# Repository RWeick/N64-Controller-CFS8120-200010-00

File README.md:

# N64-Controller-CFS8120-200010-00
The Kicad files for one variant of the N64 Controller PCB

PCB Thickness: 1.6 mm

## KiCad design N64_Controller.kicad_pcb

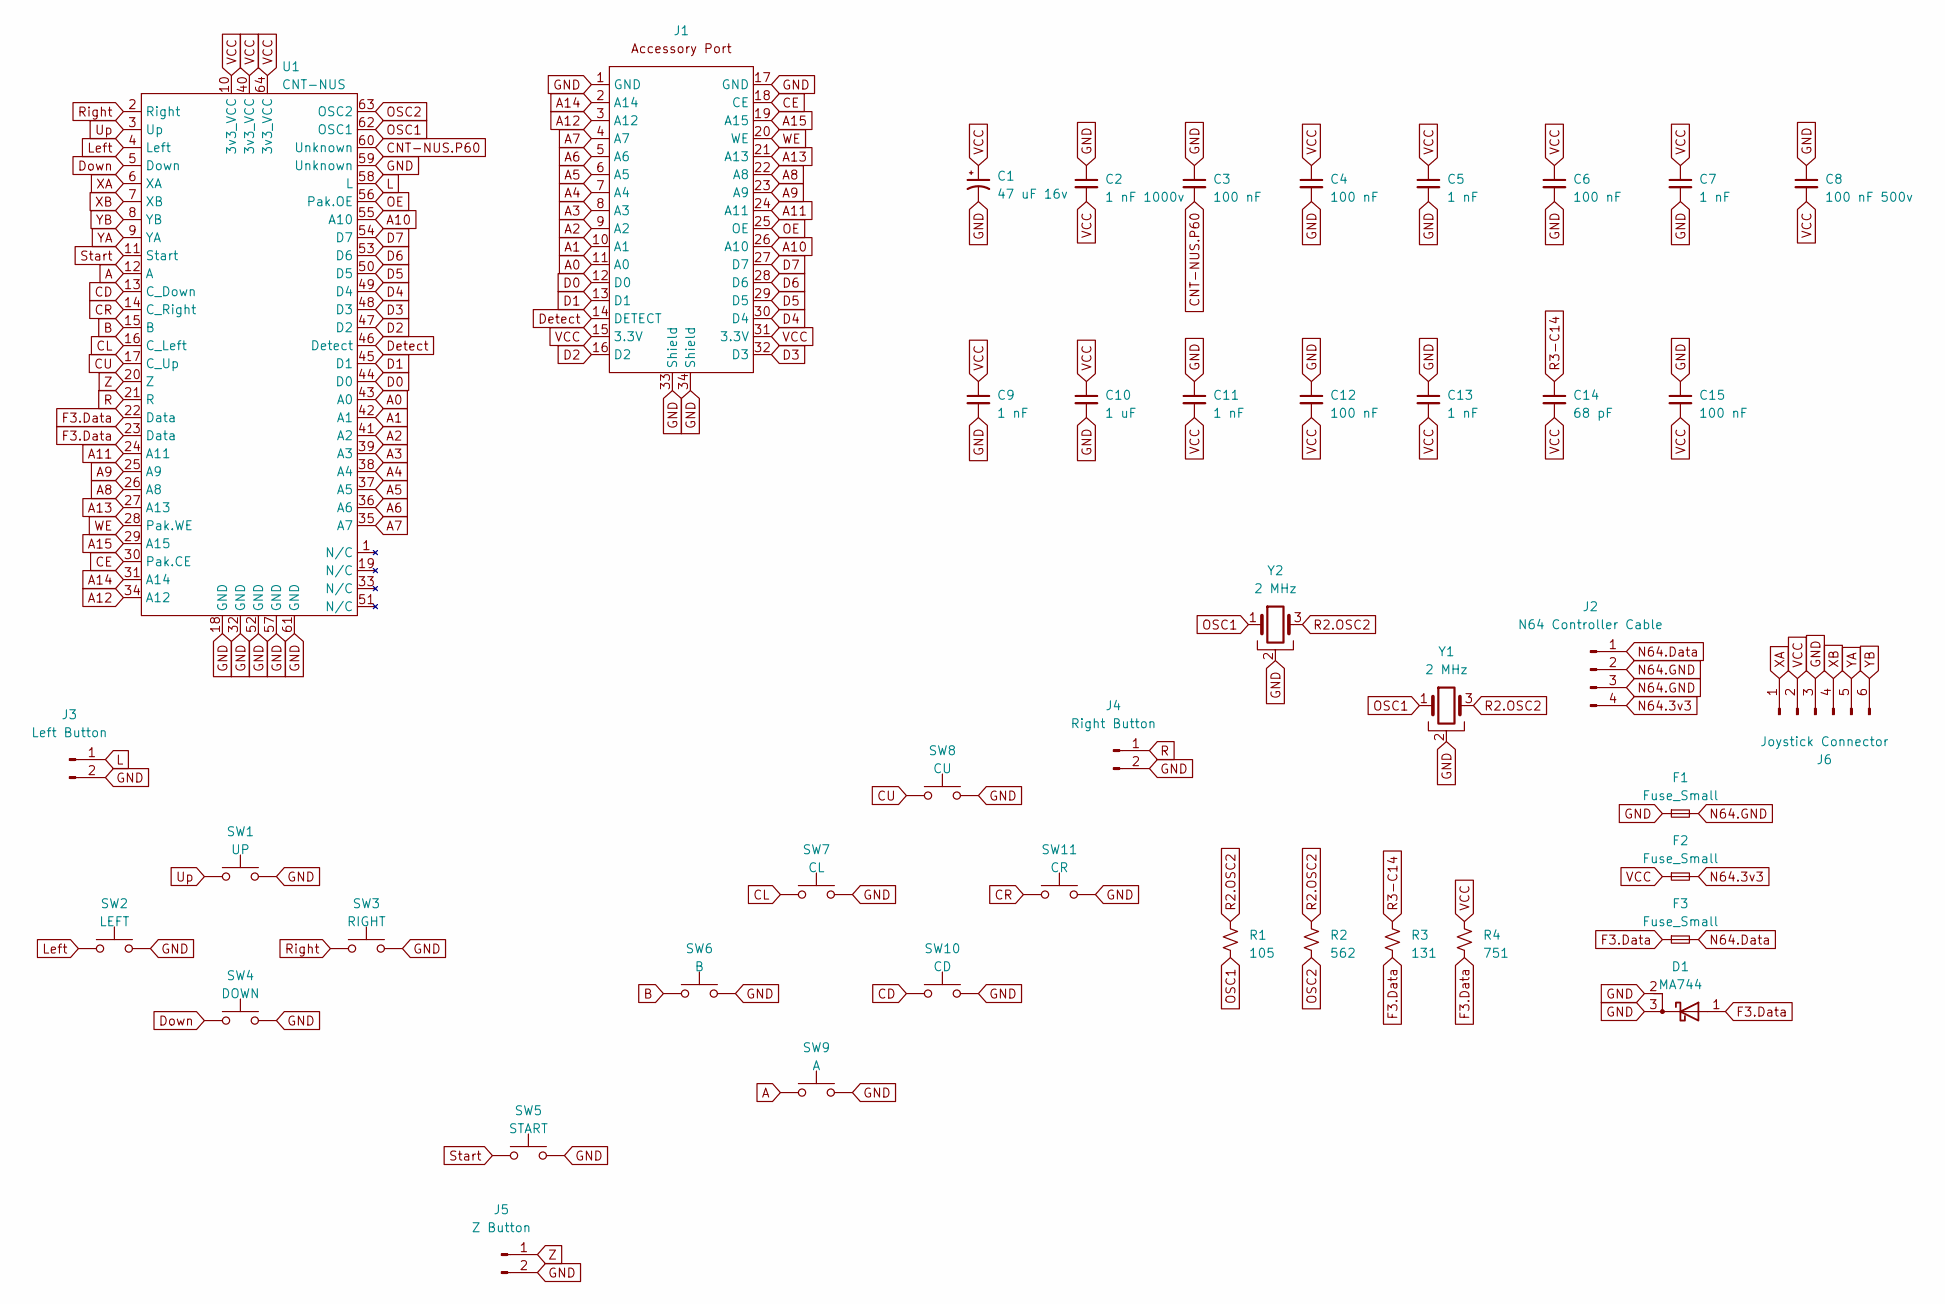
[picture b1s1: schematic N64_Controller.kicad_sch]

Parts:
C1: 47 uF 16v; CP_Radial_D5.0mm_P2.50mm
C2: 1 nF 1000v; TH Capacitor
C3, C4, C6, C12, C15: 100 nF; Small SMD
C5, C7, C9, C11, C13: 1 nF; Small SMD
C8: 100 nF 500v; TH Capacitor
C10: 1 uF; Small SMD
C14: 68 pF; Small SMD
D1: MA744; SOT-23 Diode
F1, F2, F3: Fuse_Small; SMD Fuse
J1: Accessory Port
J2: N64 Controller Cable; N64 Plug Cable Connector
J3: Left Button; Button Board Connector
J4: Right Button; Button Board Connector
J5: Z Button; Button Board Connector
J6: Joystick Connector
R1: 105; Large SMD
R2: 562; Large SMD
R3: 131; Small SMD
R4: 751; Small SMD
SW1: UP; D-Pad Button
SW2: LEFT; D-Pad Button
SW3: RIGHT; D-Pad Button
SW4: DOWN; D-Pad Button
SW5: START; Start Button
SW6: B; B Button
SW7: CL; CL Button
SW8: CU; CU Button
SW9: A; A Button
SW10: CD; CD Button
SW11: CR; CR Button
U1: CNT-NUS
Y1: 2 MHz; 2 MHz Oscillator
Y2: 2 MHz; 2 Mhz Oscillator SMD

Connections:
A: SW9.1, U1.12 (A)
A0: J1.11 (A0), U1.43 (A0)
A1: J1.10 (A1), U1.42 (A1)
A2: J1.9 (A2), U1.41 (A2)
A3: J1.8 (A3), U1.39 (A3)
A4: J1.7 (A4), U1.38 (A4)
A5: J1.6 (A5), U1.37 (A5)
A6: J1.5 (A6), U1.36 (A6)
A7: J1.4 (A7), U1.35 (A7)
A8: J1.22 (A8), U1.26 (A8)
A9: J1.23 (A9), U1.25 (A9)
A10: J1.26 (A10), U1.55 (A10)
A11: J1.24 (A11), U1.24 (A11)
A12: J1.3 (A12), U1.34 (A12)
A13: J1.21 (A13), U1.27 (A13)
A14: J1.2 (A14), U1.31 (A14)
A15: J1.19 (A15), U1.29 (A15)
B: SW6.1, U1.15 (B)
CD: SW10.1, U1.13 (C_Down)
CE: J1.18 (CE), U1.30 (Pak.CE)
CL: SW7.1, U1.16 (C_Left)
CNT-NUS.P60: C3.2, U1.60 (Unknown)
CR: SW11.1, U1.14 (C_Right)
CU: SW8.1, U1.17 (C_Up)
D0: J1.12 (D0), U1.44 (D0)
D1: J1.13 (D1), U1.45 (D1)
D2: J1.16 (D2), U1.47 (D2)
D3: J1.32 (D3), U1.48 (D3)
D4: J1.30 (D4), U1.49 (D4)
D5: J1.29 (D5), U1.50 (D5), U1.51 (D5)
D6: J1.28 (D6), U1.53 (D6)
D7: J1.27 (D7), U1.54 (D7)
Detect: J1.14 (DETECT), U1.46 (Detect)
Down: SW4.1, U1.5 (Down)
F3.Data: D1.1 (A), F3.1, R3.2, R4.2, U1.22 (Data), U1.23 (Data)
GND: C1.2, C2.1, C3.1, C4.2, C5.2, C6.2, C7.2, C8.1, C9.2, C10.2, C11.1, C12.1, C13.1, C15.1, D1.2 (K), D1.3 (K), F1.1, J1.1 (GND), J1.17 (GND), J1.33 (Shield), J1.34 (Shield), J3.2, J4.2, J5.2, J6.3, SW1.2, SW2.2, SW3.2, SW4.2, SW5.2, SW6.2, SW7.2, SW8.2, SW9.2, SW10.2, SW11.2, U1.18 (GND), U1.19 (Unknown), U1.32 (GND), U1.52 (GND), U1.57 (GND), U1.59 (Unknown), U1.61 (GND), Y1.2, Y2.2
L: J3.1, U1.58 (L)
Left: SW2.1, U1.4 (Left)
N64.3v3: F2.2, J2.4
N64.Data: F3.2, J2.1
N64.GND: F1.2, J2.2, J2.3
OE: J1.25 (OE), U1.56 (Pak.OE)
OSC2: R2.2, U1.63 (OSC2)
R: J4.1, U1.21 (R)
R3-C14: C14.1, R3.1
Right: SW3.1, U1.2 (Right)
Start: SW5.1, U1.11 (Start)
Up: SW1.1, U1.3 (Up)
VCC: C1.1, C2.2, C4.1, C5.1, C6.1, C7.1, C8.2, C9.1, C10.1, C11.2, C12.2, C13.2, C14.2, C15.2, F2.1, J1.15 (3.3V), J1.31 (3.3V), J6.2, R4.1, U1.1 (3v3_VCC), U1.10 (3v3_VCC), U1.33 (3v3_VCC), U1.40 (3v3_VCC), U1.64 (3v3_VCC)
WE: J1.20 (WE), U1.28 (Pak.WE)
XA: J6.1, U1.6 (XA)
XB: J6.4, U1.7 (XB)
YA: J6.5, U1.9 (YA)
YB: J6.6, U1.8 (YB)
Z: J5.1, U1.20 (Z)

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
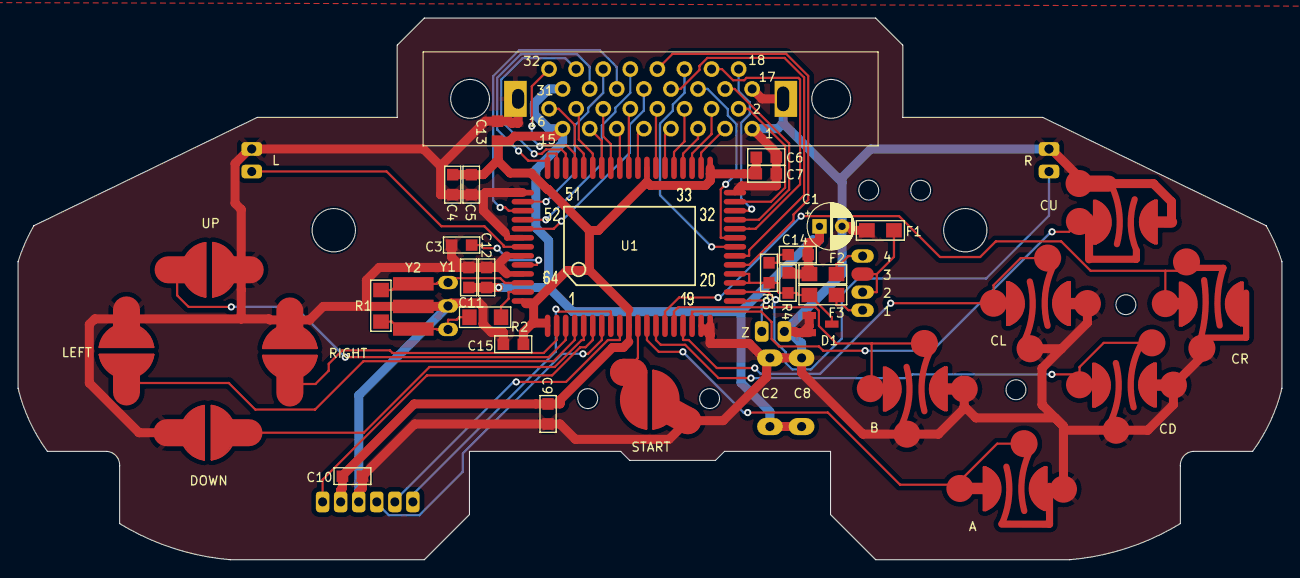
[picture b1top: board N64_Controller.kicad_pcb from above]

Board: 2 copper layers, 140.0 x 60.0 mm, 51 parts (0 on the bottom side), 57 nets.

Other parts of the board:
H1, H6: MountingHole_4.5mm
H2, H3, H4, H5, H7, H8: MountingHole_2.2mm_M2
